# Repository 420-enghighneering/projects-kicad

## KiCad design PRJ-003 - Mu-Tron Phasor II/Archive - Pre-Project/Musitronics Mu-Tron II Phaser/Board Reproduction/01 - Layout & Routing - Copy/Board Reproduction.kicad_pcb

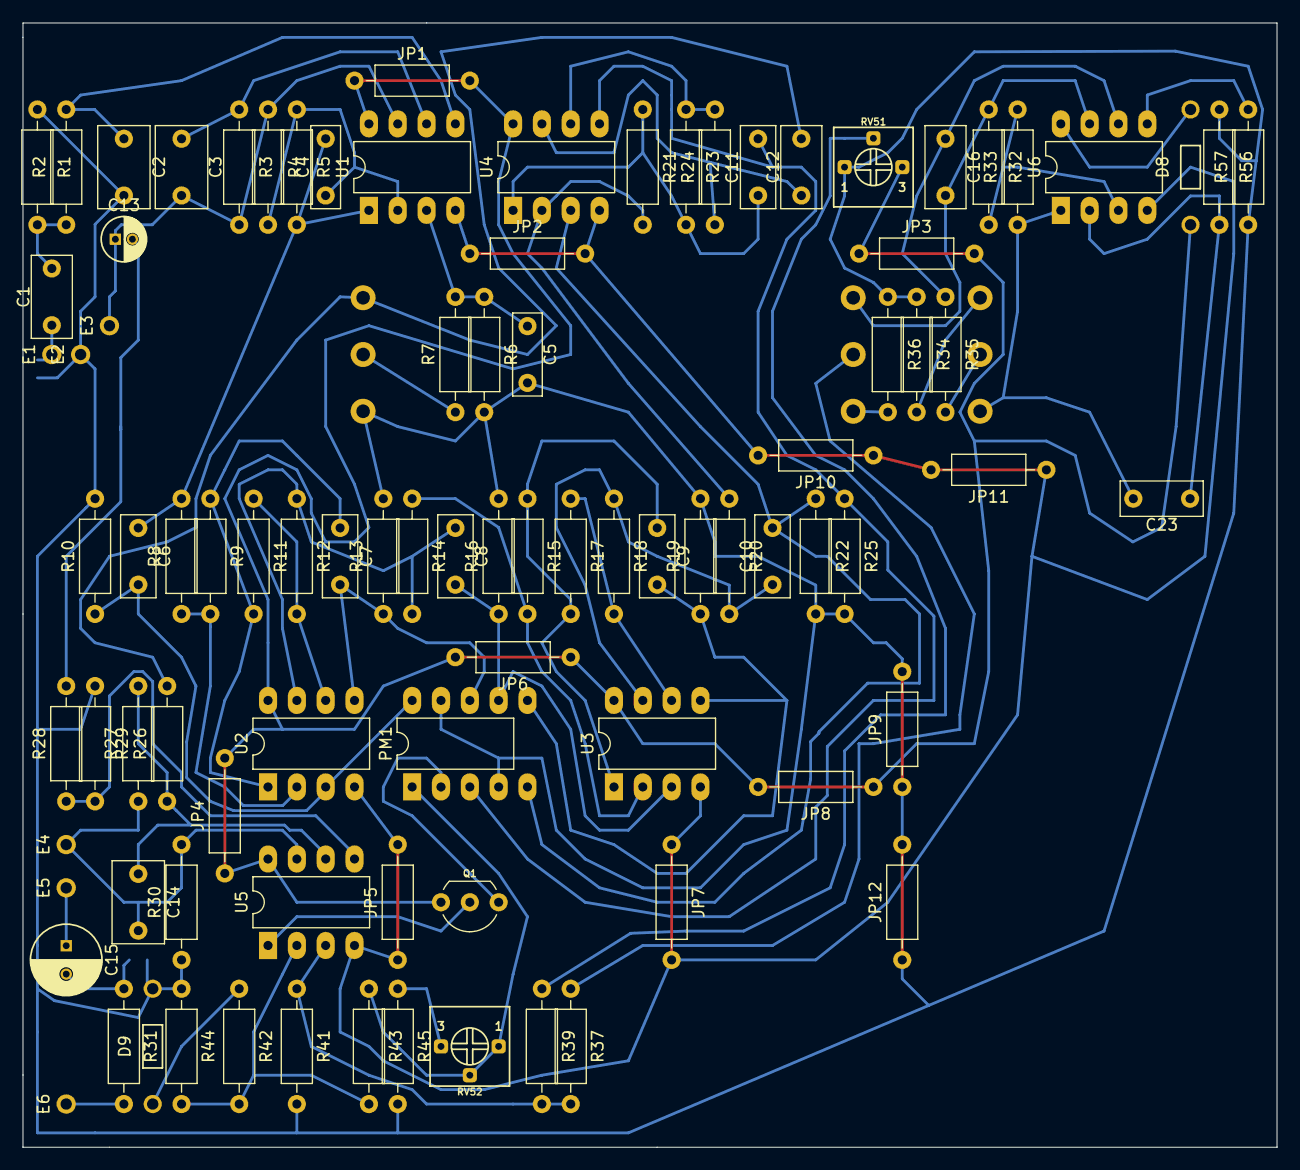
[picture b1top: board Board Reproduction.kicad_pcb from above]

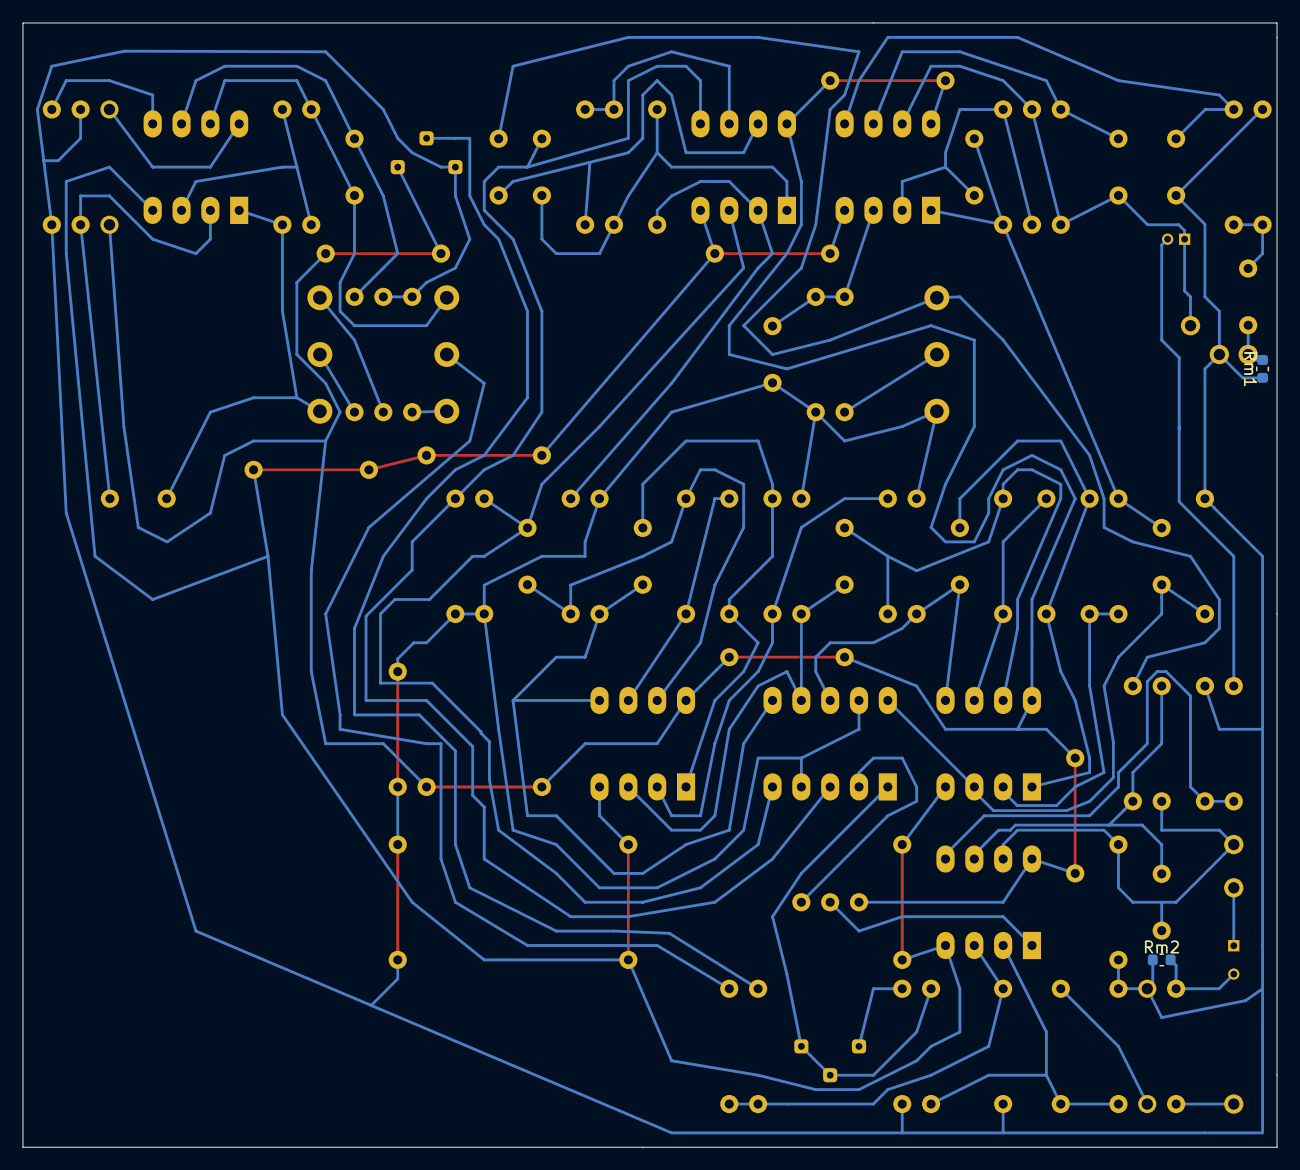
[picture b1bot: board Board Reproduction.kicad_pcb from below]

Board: 2 copper layers, 110.5 x 99.1 mm, 97 parts (2 on the bottom side), 56 nets.

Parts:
C1: 47n; Wima_MKS2F024701C00KSSD
C2: 33p; Wima_FKP2J001001D00JSSD
C3: 100n; Wima_MKS2F031001E00KSSD
C4: 1n; Wima_FKS2G011001A00KSSD
C5: 3n3; Wima_FKS2G013301A00KSSD
C6, C7, C8, C9, C10, C11, C23: 6n8; Wima_FKS2G016801B00KSSD
C12, C16: 470n; Wima_MKS2C034701C00KSSD
C13: 1u; 1.0uF_50V_4x5x1.5_UMA1H010MDD
C14: 820p; Wima_FKP2J006801D00JSSD
C15: 10u; 10uF_50V_6.3x5x2.5_UMA1H100MDD
D8: 1N4148WS; DO-35_P10.16
D9: 4148; DO-35_P10.16
E1: Input; Wire_Pad_1x01
E2: Ground; Wire_Pad_1x01
E3: SW_NO; Wire_Pad_1x01
E4: SW_NC; Wire_Pad_1x01
E5: SW_COM; Wire_Pad_1x01
E6: Output; Wire_Pad_1x01
JP1, JP2, JP3, JP4, JP5, JP6, JP7, JP8, JP9, JP10, JP11, JP12: 0R; R_CF25_P10.16_H
PM1: Photomodule
Q1: ON_Semi_2N3904TAR
R1, R3: 390k; R_CC25_P10.16_H
R2: 3k9; R_CC25_P10.16_H
R4, R5, R6, R8, R9, R11, R12, R14, R15, R17, R18, R20, R21, R23, R24: 4k7; R_CC25_P10.16_H
R7, R27, R29: 8k2; R_CC25_P10.16_H
R10, R13, R16, R19, R22, R25, R43: 220k; R_CC25_P10.16_H
R26, R28, R42: 10k; R_CC25_P10.16_H
R30, R35, R57: 27k; R_CC25_P10.16_H
R31, R36: 560R; R_CC25_P10.16_H
R32, R39: 47k; R_CC25_P10.16_H
R33: 56k; R_CC25_P10.16_H
R34: 82R; R_CC25_P10.16_H
R37: 82k; R_CC25_P10.16_H
R41: 3k3; R_CC25_P10.16_H
R44: 68k; R_CC25_P10.16_H
R45: 220R; R_CC25_P10.16_H
R56: 100k; R_CC25_P10.16_H
RV51: 10k; Bourns_3362P-1-104
RV52: 1k; Bourns_3362P-1-104
RV53, RV54: B10k; Alpha_Taiwan_RV16AF-41
RV55: A25k; Alpha_Taiwan_RV16AF-41
Rm1, Rm2: 1M; R_0603_1608M
U1, U2, U3, U4, U5, U6: 4558; Texas_Instruments_RC4558P

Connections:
GND: C2.2, C5.2, D9.2, E2.1, JP9.1, JP9.2, JP12.1, JP12.2, PM1.4, PM1.9, R1.1, R6.2, R10.2, R13.2, R16.2, R19.2, R22.2, R25.2, R29.1, R30.1, R34.1, R36.1, R41.2, R44.1, R45.2, R56.1, R57.1, RV51.1, RV53.1, Rm1.1, Rm2.1
unnamed: C1.2, R1.2, R2.1
unnamed: C2.1, R2.2, U1.5
unnamed: C3.1, R3.1, U1.6
unnamed: C4.1, R4.2, R5.1, U1.2
unnamed: C5.1, R6.1, R7.2, U1.3
unnamed: C6.2, PM1.10, R10.1, U2.3
unnamed: C7.1, R9.1, R11.2, U2.1
unnamed: C7.2, PM1.8, R13.1, U2.5
unnamed: C8.1, R12.1, R14.2, U2.7
unnamed: C8.2, PM1.7, R16.1, U3.3
unnamed: C9.1, R15.1, R17.2, U3.1
unnamed: C9.2, PM1.6, R19.1, U3.5
unnamed: C10.1, R18.1, R20.2, U3.7
unnamed: C10.2, PM1.5, R22.1, U4.3
unnamed: C11.1, R21.1, R23.2, U4.1
unnamed: C11.2, PM1.3, R25.1, U4.5
unnamed: C12.2, R26.2, RV53.3
unnamed: C3.2, C13.1, E3.1, R3.2, R4.1, U1.7
unnamed: C13.2, R28.2
unnamed: C14.1, R26.1, R27.2, U5.6
unnamed: C14.2, E4.1, R27.1, R30.2, U5.7
unnamed: C15.1, E5.1
unnamed: C15.2, R31.1, Rm2.2
unnamed: C16.1, R35.1, U6.6
unnamed: C16.2, R32.1, RV54.3, U6.7
unnamed: C23.1, R56.2, U6.2
unnamed: C23.2, R33.1, RV55.3, U6.1
unnamed: D8.2, U6.8
unnamed: D9.1, R42.1
unnamed: PM1.1, R43.1, RV52.1, RV52.2
unnamed: PM1.2, Q1.1
unnamed: Q1.2, U5.1
unnamed: R8.1, R9.2, U2.2
unnamed: R11.1, R12.2, U2.6
unnamed: R14.1, R15.2, U3.2
unnamed: R17.1, R18.2, U3.6
unnamed: R20.1, R21.2, U4.2
unnamed: R23.1, R24.2, U4.6
unnamed: R28.1, R29.2, U5.5
unnamed: R32.2, R33.2, U6.3
unnamed: R34.2, RV55.1
unnamed: R35.2, RV55.2
unnamed: R36.2, RV54.1
unnamed: R37.1, RV54.2
unnamed: R37.2, R39.2, R41.1, U5.3
unnamed: R39.1, RV51.2
unnamed: R42.2, R43.2, R44.2, U5.2
unnamed: R45.1, RV52.3
unnamed: R57.2, U6.5
PHASER_IN: C4.2, C6.1, R5.2, R8.2, U1.1
PHASER_OUT: C12.1, R24.1, U4.7
RETURN: E6.1, R31.2
SEND: C1.1, E1.1, Rm1.2
VCC: D8.1, JP1.1, JP1.2, JP3.1, JP3.2, JP4.1, JP4.2, JP6.1, JP6.2, JP8.1, JP8.2, Q1.3, RV51.3, U1.8, U2.8, U3.8, U4.8, U5.8
VSS: JP2.1, JP2.2, JP5.1, JP5.2, JP7.1, JP7.2, JP10.1, JP10.2, JP11.1, JP11.2, U1.4, U2.4, U3.4, U4.4, U5.4, U6.4

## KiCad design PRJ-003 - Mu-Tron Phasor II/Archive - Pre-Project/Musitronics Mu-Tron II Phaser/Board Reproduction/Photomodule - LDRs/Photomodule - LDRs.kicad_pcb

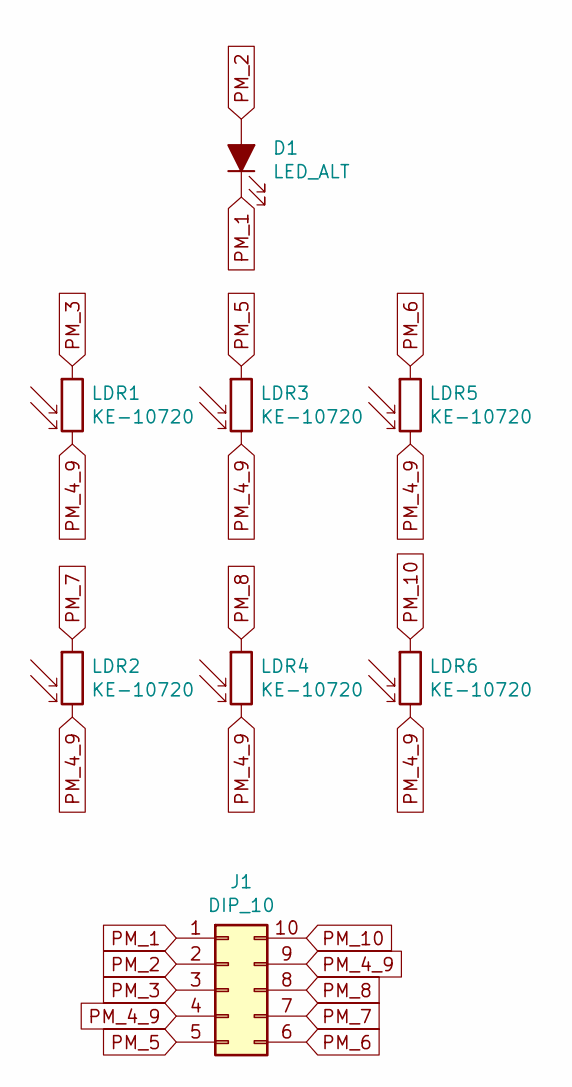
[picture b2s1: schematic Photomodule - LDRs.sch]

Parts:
D1: LED_ALT; DO-41_P2.54
J1: DIP_10; Photomodule
LDR1, LDR2, LDR3, LDR4, LDR5, LDR6: KE-10720; Waitrony_KE-10720

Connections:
PM_1: D1.1 (K), J1.1
PM_2: D1.2 (A), J1.2
PM_3: J1.3, LDR1.1
PM_4_9: J1.4, J1.9, LDR1.2, LDR2.2, LDR3.2, LDR4.2, LDR5.2, LDR6.2
PM_5: J1.5, LDR3.1
PM_6: J1.6, LDR5.1
PM_7: J1.7, LDR2.1
PM_8: J1.8, LDR4.1
PM_10: J1.10, LDR6.1

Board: 2 copper layers, 8 parts (0 on the bottom side), 9 nets, no tracks yet.

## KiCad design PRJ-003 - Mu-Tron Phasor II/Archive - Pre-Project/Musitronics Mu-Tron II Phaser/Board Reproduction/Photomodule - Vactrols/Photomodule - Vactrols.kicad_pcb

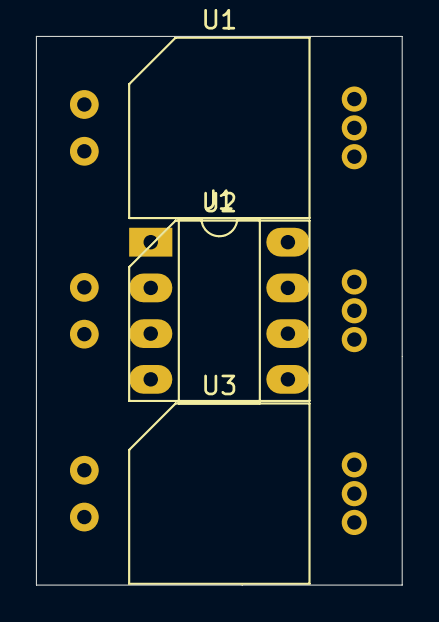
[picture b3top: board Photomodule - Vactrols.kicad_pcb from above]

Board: 2 copper layers, 20.3 x 30.5 mm, 4 parts (0 on the bottom side), 8 nets, no tracks yet.

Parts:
J1: DIP_10; Texas_Instruments_RC4558P
U1, U2, U3: Xvive_VTL5C3_2

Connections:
PM_1: J1.1, U1.1, U2.1, U3.1
PM_2: J1.2, U1.2, U2.2, U3.2
PM_3: J1.3, U3.5
PM_4_9: J1.4, U1.4, U2.4, U3.4
PM_5: J1.5, U3.3
PM_6: J1.6, U2.5
PM_7: J1.7, U2.3
PM_8: J1.8, U1.5

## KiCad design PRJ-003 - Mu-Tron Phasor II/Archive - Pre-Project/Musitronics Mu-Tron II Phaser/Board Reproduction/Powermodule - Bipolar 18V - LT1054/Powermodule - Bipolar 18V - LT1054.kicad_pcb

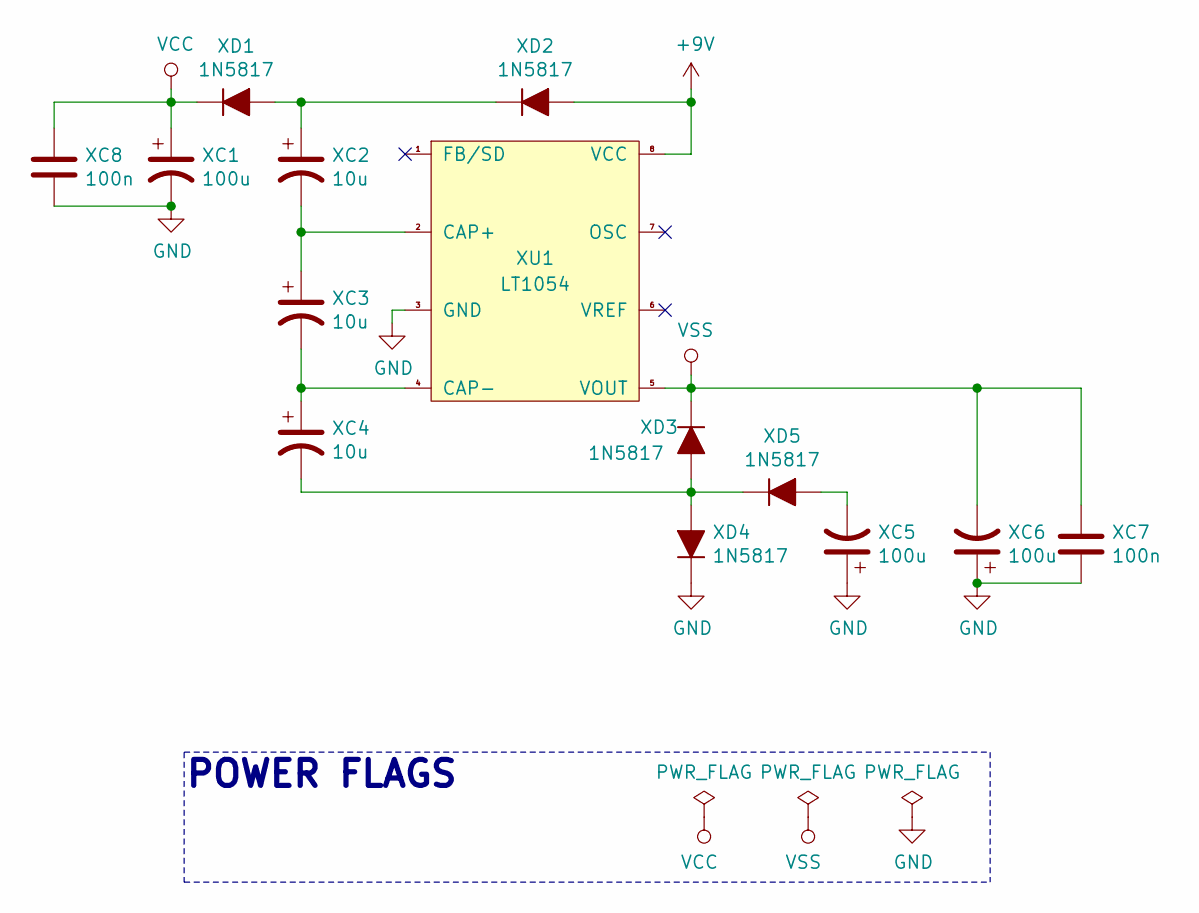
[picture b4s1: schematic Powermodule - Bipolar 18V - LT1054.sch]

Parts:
XC1, XC5, XC6: 100u; Nichicon_UMA1E101MDD_100uF_P2.50_8.0x5.0mm
XC2, XC3, XC4: 10u; Nichicon_UMA1E100MDD_10uF_P2.00_5.0x5.0mm
XC7, XC8: 100n; Wima_MKS2C031001A00KSSD
XD1, XD2, XD3, XD4, XD5: 1N5817; DO-41_P10.16
XU1: LT1054

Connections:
+9V: XD2.1 (A), XU1.8 (VCC)
GND: XC1.2, XC5.1, XC6.1, XC7.2, XC8.2, XD4.2 (K), XU1.3 (GND)
unnamed: XC2.1, XD1.1 (A), XD2.2 (K)
unnamed: XC2.2, XC3.1, XU1.2 (CAP+)
unnamed: XC3.2, XC4.1, XU1.4 (CAP-)
unnamed: XC4.2, XD3.1 (A), XD4.1 (A), XD5.2 (K)
unnamed: XC5.2, XD5.1 (A)
VCC: XC1.1, XC8.1, XD1.2 (K)
VSS: XC6.2, XC7.1, XD3.2 (K), XU1.5 (VOUT)

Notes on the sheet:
POWER FLAGS

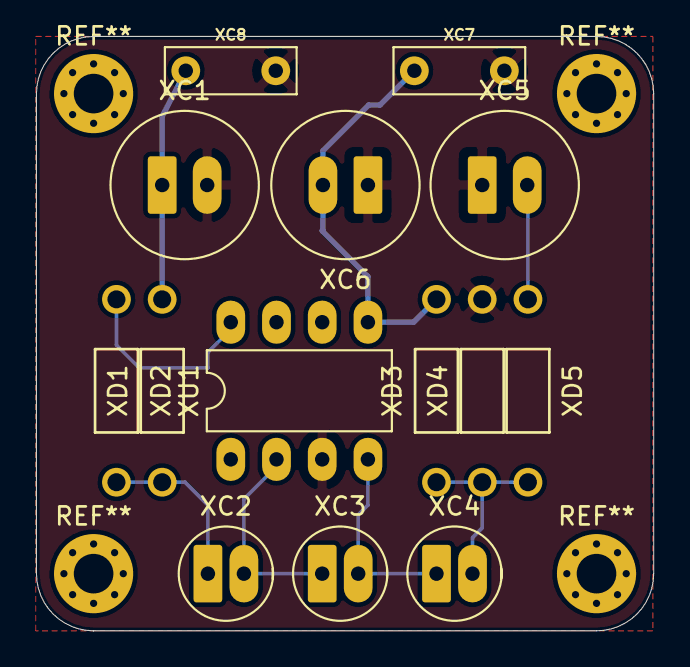
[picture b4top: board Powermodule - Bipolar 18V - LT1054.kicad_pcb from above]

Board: 2 copper layers, 34.3 x 33.0 mm, 14 parts (0 on the bottom side), 9 nets.

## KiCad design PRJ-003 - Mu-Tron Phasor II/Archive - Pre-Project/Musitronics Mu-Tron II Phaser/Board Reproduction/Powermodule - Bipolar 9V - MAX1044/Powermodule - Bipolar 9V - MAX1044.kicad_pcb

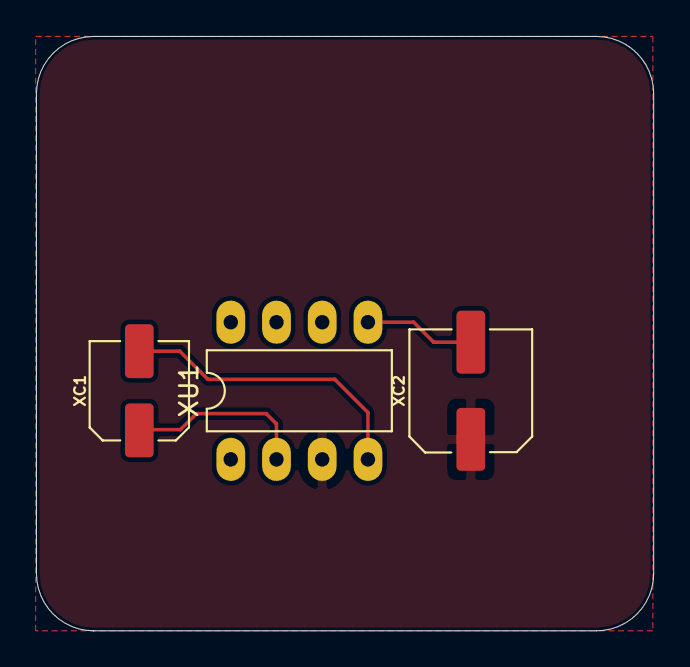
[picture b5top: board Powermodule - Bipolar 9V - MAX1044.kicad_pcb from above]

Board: 2 copper layers, 34.3 x 33.0 mm, 3 parts (0 on the bottom side), 5 nets.

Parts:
XC1: 10u; Nichicon_UWT1V100MCL1GB
XC2: 47u; Nichicon_UWT1V470MCL1GS
XU1: MAX1044CPA

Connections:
+9V: XU1.1, XU1.8
-9V: XC2.2, XU1.5
GND: XC2.1, XU1.3
unnamed: XC1.1, XU1.2
unnamed: XC1.2, XU1.4
